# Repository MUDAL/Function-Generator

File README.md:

# Function-Generator

## Description  

This custom function generator is capable of outputting sine, square, and triangle waves of variable amplitude and frequency. An extra requirement of this device is its ability to produce DC voltages of adjustable magnitude and polarity.  

## Repository Layout
```
.
├── 3D_Models
├── Diagrams
├── Firmware
├── Images
├── LICENSE
├── PCB
├── README.md
└── Simulation
```

## Video Demos  
1. [Introduction and setup](https://drive.google.com/file/d/1G1p_1wfvQfPOZcchX9nzK7hOxaMMsMGi/view?usp=sharing)  
2. [System components](https://drive.google.com/file/d/1G7yjkzn5fIc1sIlq5uEcu3o-C55AYfCc/view?usp=sharing)   
3. [Amplitude control](https://drive.google.com/file/d/1G8uY1fm0E4KQyqx2Z7YYd4BkqQ50rcqq/view?usp=drive_link)    
4. [Waveform selection](https://drive.google.com/file/d/1GDZh32V0VEGifeL3dQ4JVQDjZ7OjrVeD/view?usp=sharing)   
5. [Frequency adjustment](https://drive.google.com/file/d/1HKlgbLmxHBRYYwaI7JoV4cJPAN9Vxr-B/view?usp=sharing)   
6. [DC magnitude and polarity control](https://drive.google.com/file/d/1HQdHPNzv4oxDs-NsEo27Fcs3HjVcjQDH/view?usp=sharing)    

## Images

## Helpful resources  
- [Rail splitter circuit with virtual push-pull topology: Discussion on EEVBlog](https://www.eevblog.com/forum/beginners/virtual-ground-push-pull/)
- [How the power supply rail splitter circuit works: An article written by Apichet Garaipoom](https://www.eleccircuit.com/power-supply-splitter-circuit-using-op-amp/)
- [EEVBlog discussion on high speed operational amplifiers](https://www.eevblog.com/forum/beginners/op-amp-bandwidth-and-is-there-an-affordable-fast-op-amp/)    
- [What is Slew Rate all about?](https://www.sciencedirect.com/topics/engineering/slew-rate)
- [Reddit discussion on high speed operational amplifiers](https://www.reddit.com/r/AskElectronics/comments/186d19x/high_speed_high_power_opamps/?rdt=65066)
- [Ivanchenko59: AD9833-DDS-Generator STM32 library](https://github.com/Ivanchenko59/AD9833-DDS-Generator/tree/master)
- [Mahamudul Hasan: Interfacing STM32 with I2C LCD: HAL example code included](https://embeddedthere.com/interfacing-stm32-with-i2c-lcd-with-hal-code-example/)
- [AD9833 Programmable Waveform Generator: Datasheet](https://www.analog.com/media/en/technical-documentation/data-sheets/AD9833.pdf)
- [STM32 Blue Pill 3D model by Denshi Kousaku](https://grabcad.com/library/stm32f103c8t6-blue-pill-board-1)
- [BNC Connector 3D model by Daniel Forero Morales](https://grabcad.com/library/bnc-connector--2)

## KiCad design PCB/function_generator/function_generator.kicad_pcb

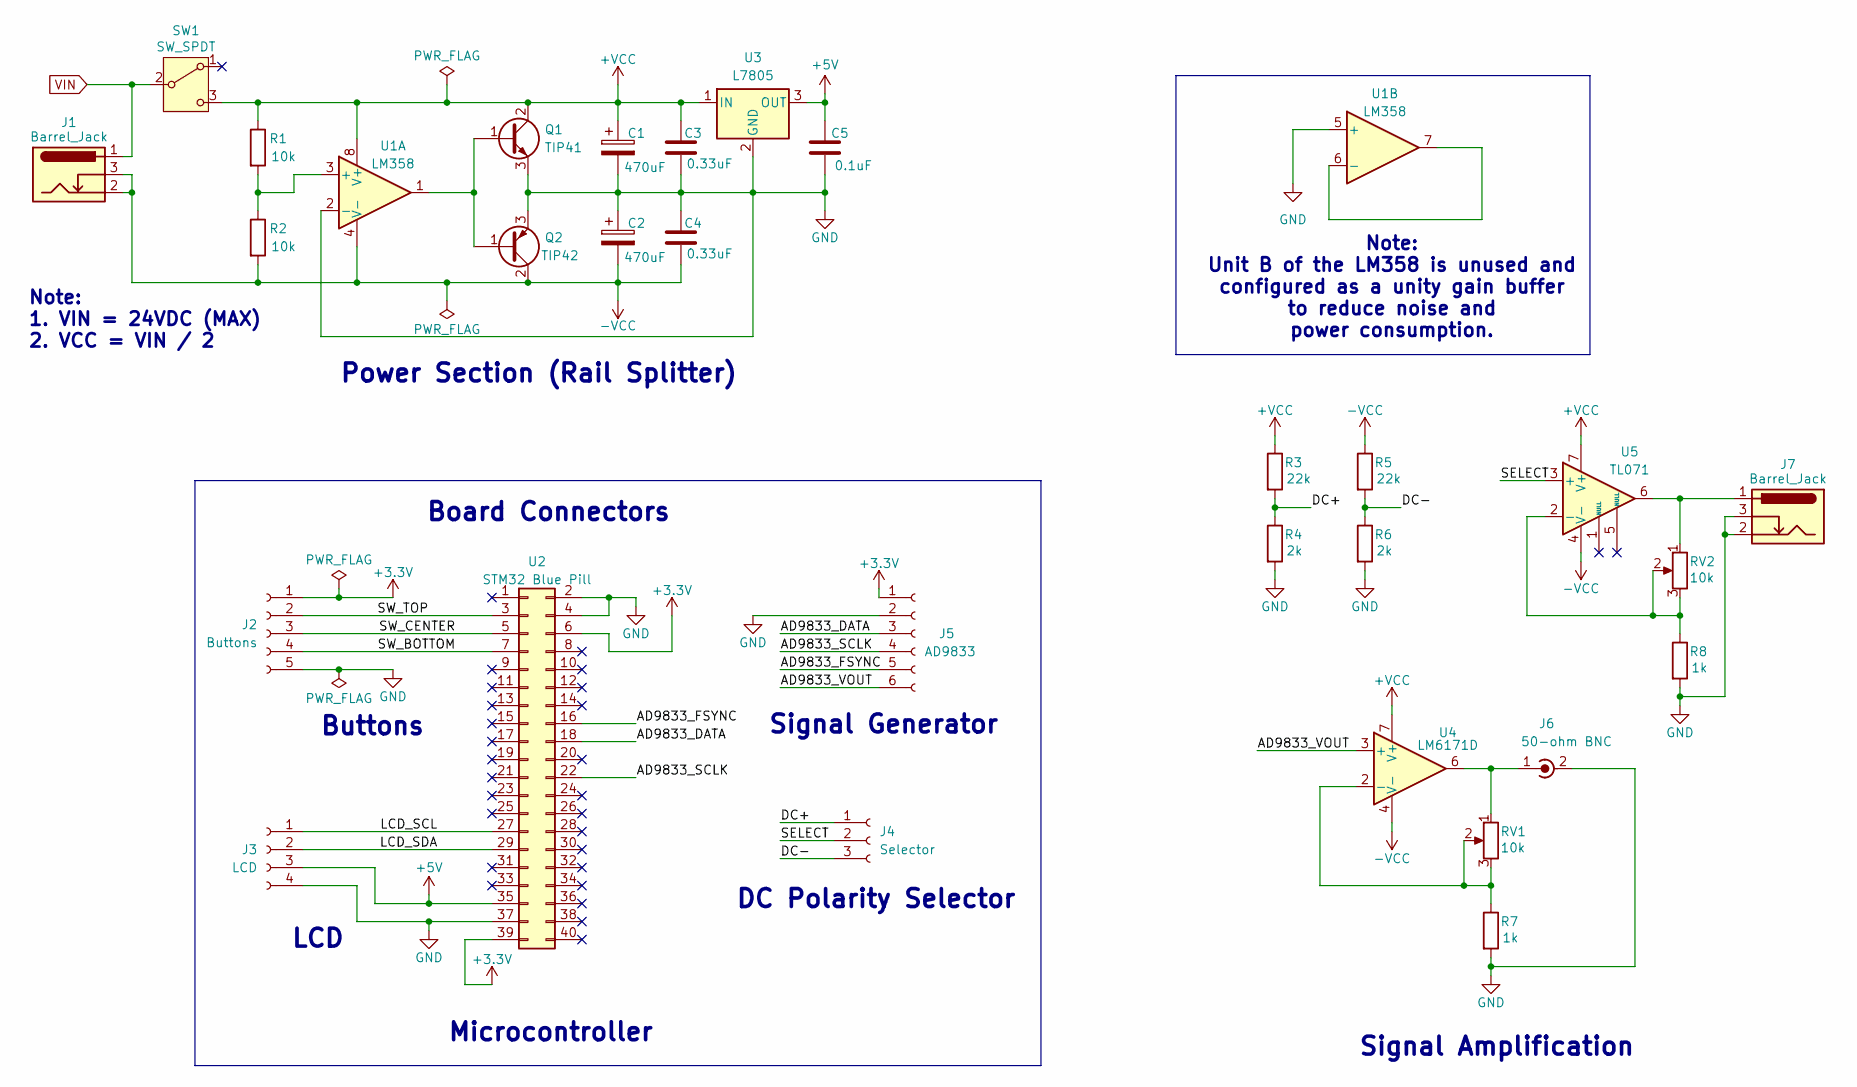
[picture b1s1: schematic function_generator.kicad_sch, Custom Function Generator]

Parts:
C1, C2: 470uF; CP_Radial_D10.0mm_P5.00mm
C3, C4: 0.33uF; C_Disc_D4.3mm_W1.9mm_P5.00mm
C5: 0.1uF; C_Disc_D4.3mm_W1.9mm_P5.00mm
J1, J7: Barrel_Jack; PinHeader_1x03_P2.54mm_Vertical
J2: Buttons; PinHeader_1x05_P2.54mm_Vertical
J3: LCD; PinHeader_1x04_P2.54mm_Vertical
J4: Selector; PinHeader_1x03_P2.54mm_Vertical
J5: AD9833; PinSocket_1x06_P2.54mm_Vertical
J6: 50-ohm BNC; BNC_Amphenol_B6252HB-NPP3G-50_Horizontal
Q1: TIP41; TO-220-3_Vertical
Q2: TIP42; TO-220-3_Vertical
R1, R2: 10k; R_Axial_DIN0207_L6.3mm_D2.5mm_P7.62mm_Horizontal
R3, R5: 22k; R_Axial_DIN0207_L6.3mm_D2.5mm_P7.62mm_Horizontal
R4, R6: 2k; R_Axial_DIN0207_L6.3mm_D2.5mm_P7.62mm_Horizontal
R7, R8: 1k; R_Axial_DIN0207_L6.3mm_D2.5mm_P7.62mm_Horizontal
RV1, RV2: 10k; PinHeader_1x03_P2.54mm_Vertical
SW1: SW_SPDT; PinHeader_1x03_P2.54mm_Vertical
U1: LM358; DIP-8_W7.62mm
U2: STM32 Blue Pill; Blue_Pill
U3: L7805; TO-220-3_Vertical
U4: LM6171D; SOIC-8_3.9x4.9mm_P1.27mm
U5: TL071; DIP-8_W7.62mm

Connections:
+3.3V: J2.1, J5.1, U2.6, U2.39
+5V: C5.1, J3.3, U2.35, U3.3 (OUT)
+VCC: C1.1, C3.1, Q1.2 (C), R1.1, R3.1, SW1.3 (C), U1.8 (V+), U3.1 (IN), U4.7 (V+), U5.7 (V+)
-VCC: C2.2, C4.2, J1.2, J1.3, Q2.2 (C), R2.2, R5.1, U1.4 (V-), U4.4 (V-), U5.4 (V-)
/AD9833_DATA: J5.3, U2.18
/AD9833_FSYNC: J5.5, U2.16
/AD9833_SCLK: J5.4, U2.22
/AD9833_VOUT: J5.6, U4.3 (+)
/DC+: J4.1, R3.2, R4.1
/DC-: J4.3, R5.2, R6.1
/LCD_SCL: J3.1, U2.27
/LCD_SDA: J3.2, U2.29
/SELECT: J4.2, U5.3 (+)
/SW_BOTTOM: J2.4, U2.7
/SW_CENTER: J2.3, U2.5
/SW_TOP: J2.2, U2.3
GND: C1.2, C2.1, C3.2, C4.1, C5.2, J2.5, J3.4, J5.2, J6.2 (Ext), J7.2, J7.3, Q1.3 (E), Q2.3 (E), R4.2, R6.2, R7.2, R8.2, U1.2 (-), U1.5 (+), U2.2, U2.4, U2.37, U3.2 (GND)
unnamed: J6.1 (In), RV1.1, U4.6
unnamed: J7.1, RV2.1, U5.6
unnamed: Q1.1 (B), Q2.1 (B), U1.1
unnamed: R1.2, R2.1, U1.3 (+)
unnamed: U1.6 (-), U1.7
unnamed: R7.1, RV1.2, RV1.3, U4.2 (-)
unnamed: R8.1, RV2.2, RV2.3, U5.2 (-)
VIN: J1.1, SW1.2 (B)

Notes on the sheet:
Board Connectors
LCD
Signal Amplification
Microcontroller
Note: 1. VIN = 24VDC (MAX) 2. VCC = VIN / 2
Signal Generator
DC Polarity Selector
Power Section (Rail Splitter)
Note: Unit B of the LM358 is unused and configured as a unity gain buffer to reduce noise and power consumption.
Buttons

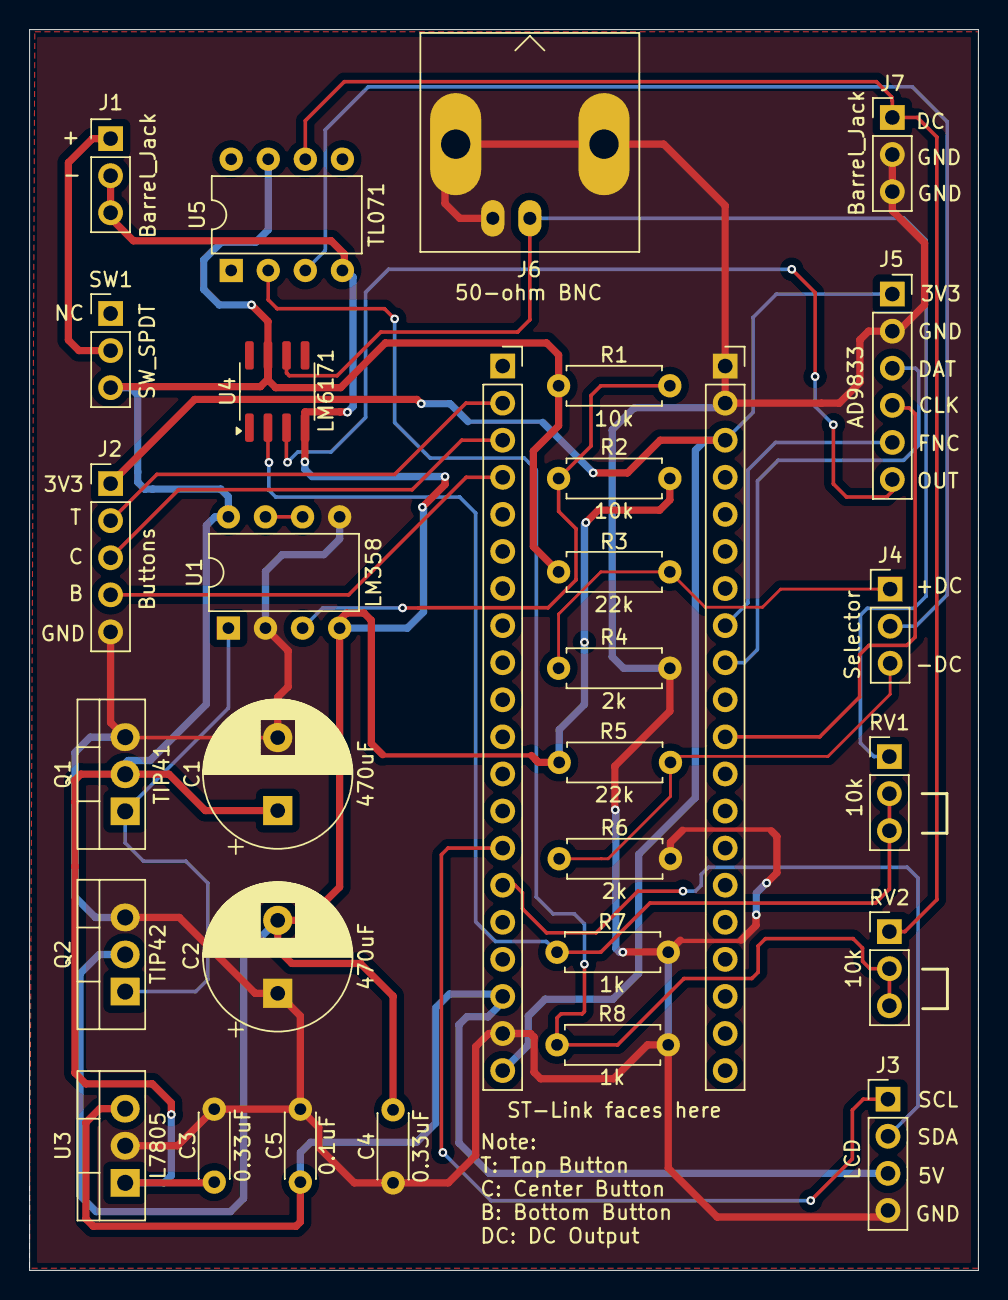
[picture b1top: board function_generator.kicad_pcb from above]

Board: 2 copper layers, 65.0 x 85.0 mm, 30 parts (0 on the bottom side), 25 nets.

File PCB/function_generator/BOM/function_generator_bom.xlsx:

Reference | Qty | Description | Manufacturer | Value | Footprint | DNP | Notes
U5 | 1 | Single Low-Noise JFET-Input Operational Amplifiers, DIP-8/SOIC-8 |  | TL071 | Package_DIP:DIP-8_W7.62mm | DNP
Q2 | 1 | -6A Ic, -40V Vce, Power PNP Transistor, TO-220 |  | TIP42 | Package_TO_SOT_THT:TO-220-3_Vertical | DNP
Q1 | 1 | 6A Ic, 40V Vce, Power NPN Transistor, TO-220 |  | TIP41 | Package_TO_SOT_THT:TO-220-3_Vertical | DNP
SW1 | 1 | Switch, single pole double throw |  | SW_SPDT | Connector_PinHeader_2.54mm:PinHeader_1x03_P2.54mm_Vertical | DNP
U2 | 1 | STM32 Blue Pill board |  | STM32 Blue Pill | Blue_Pill:Blue_Pill | DNP
J4 | 1 | Generic connector, single row, 01x03, script generated |  | Selector | Connector_PinHeader_2.54mm:PinHeader_1x03_P2.54mm_Vertical | DNP
U4 | 1 | High Speed Low Power Low Distortion Voltage Feedback Amplifier, SOIC-8 | Texas Instruments | LM6171 | Package_SO:SOIC-8_3.9x4.9mm_P1.27mm |  | SMD component. Assemble only this
U1 | 1 | Low-Power, Dual Operational Amplifiers, DIP-8/SOIC-8/TO-99-8 |  | LM358 | Package_DIP:DIP-8_W7.62mm | DNP
J3 | 1 | Generic connector, single row, 01x04, script generated |  | LCD | Connector_PinHeader_2.54mm:PinHeader_1x04_P2.54mm_Vertical | DNP
U3 | 1 | Positive 1.5A 35V Linear Regulator, Fixed Output 5V, TO-220/TO-263/TO-252 |  | L7805 | Package_TO_SOT_THT:TO-220-3_Vertical | DNP
J2 | 1 | Generic connector, single row, 01x05, script generated |  | Buttons | Connector_PinHeader_2.54mm:PinHeader_1x05_P2.54mm_Vertical | DNP
J7 | 1 | DC Barrel Jack with an internal switch |  | Barrel_Jack | Connector_PinHeader_2.54mm:PinHeader_1x03_P2.54mm_Vertical | DNP
J1 | 1 | DC Barrel Jack with an internal switch |  | Barrel_Jack | Connector_PinHeader_2.54mm:PinHeader_1x03_P2.54mm_Vertical | DNP
J5 | 1 | Generic connector, single row, 01x06, script generated |  | AD9833 | Connector_PinSocket_2.54mm:PinSocket_1x06_P2.54mm_Vertical | DNP
R5 | 1 | Resistor |  | 22k | Resistor_THT:R_Axial_DIN0207_L6.3mm_D2.5mm_P7.62mm_Horizontal | DNP
R3 | 1 | Resistor |  | 22k | Resistor_THT:R_Axial_DIN0207_L6.3mm_D2.5mm_P7.62mm_Horizontal | DNP
RV2 | 1 | Potentiometer |  | 10k | Connector_PinHeader_2.54mm:PinHeader_1x03_P2.54mm_Vertical | DNP
RV1 | 1 | Potentiometer |  | 10k | Connector_PinHeader_2.54mm:PinHeader_1x03_P2.54mm_Vertical | DNP
R2 | 1 | Resistor |  | 10k | Resistor_THT:R_Axial_DIN0207_L6.3mm_D2.5mm_P7.62mm_Horizontal | DNP
R1 | 1 | Resistor |  | 10k | Resistor_THT:R_Axial_DIN0207_L6.3mm_D2.5mm_P7.62mm_Horizontal | DNP
R6 | 1 | Resistor |  | 2k | Resistor_THT:R_Axial_DIN0207_L6.3mm_D2.5mm_P7.62mm_Horizontal | DNP
R4 | 1 | Resistor |  | 2k | Resistor_THT:R_Axial_DIN0207_L6.3mm_D2.5mm_P7.62mm_Horizontal | DNP
R8 | 1 | Resistor |  | 1k | Resistor_THT:R_Axial_DIN0207_L6.3mm_D2.5mm_P7.62mm_Horizontal | DNP
R7 | 1 | Resistor |  | 1k | Resistor_THT:R_Axial_DIN0207_L6.3mm_D2.5mm_P7.62mm_Horizontal | DNP
J6 | 1 | coaxial connector (BNC, SMA, SMB, SMC, Cinch/RCA, LEMO, ...) |  | 50-ohm BNC | Connector_Coaxial:BNC_Amphenol_B6252HB-NPP3G-50_Horizontal | DNP
C2 | 1 | Polarized capacitor |  | 470uF | Capacitor_THT:CP_Radial_D10.0mm_P5.00mm | DNP
C1 | 1 | Polarized capacitor |  | 470uF | Capacitor_THT:CP_Radial_D10.0mm_P5.00mm | DNP
C4 | 1 | Unpolarized capacitor |  | 0.33uF | Capacitor_THT:C_Disc_D4.3mm_W1.9mm_P5.00mm | DNP
C3 | 1 | Unpolarized capacitor |  | 0.33uF | Capacitor_THT:C_Disc_D4.3mm_W1.9mm_P5.00mm | DNP
C5 | 1 | Unpolarized capacitor |  | 0.1uF | Capacitor_THT:C_Disc_D4.3mm_W1.9mm_P5.00mm | DNP

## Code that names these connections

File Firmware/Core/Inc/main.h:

/* USER CODE BEGIN Header */
/**
  ******************************************************************************
  * @file           : main.h
  * @brief          : Header for main.c file.
  *                   This file contains the common defines of the application.
  ******************************************************************************
  * @attention
  *
  * <h2><center>&copy; Copyright (c) 2024 STMicroelectronics.
  * All rights reserved.</center></h2>
  *
  * This software component is licensed by ST under BSD 3-Clause license,
  * the "License"; You may not use this file except in compliance with the
  * License. You may obtain a copy of the License at:
  *                        opensource.org/licenses/BSD-3-Clause
  *
  ******************************************************************************
  */
/* USER CODE END Header */

/* Define to prevent recursive inclusion -------------------------------------*/
#ifndef __MAIN_H
#define __MAIN_H

#ifdef __cplusplus
extern "C" {
#endif

/* Includes ------------------------------------------------------------------*/
#include "stm32f1xx_hal.h"

/* Private includes ----------------------------------------------------------*/
/* USER CODE BEGIN Includes */

/* USER CODE END Includes */

/* Exported types ------------------------------------------------------------*/
/* USER CODE BEGIN ET */

/* USER CODE END ET */

/* Exported constants --------------------------------------------------------*/
/* USER CODE BEGIN EC */

/* USER CODE END EC */

/* Exported macro ------------------------------------------------------------*/
/* USER CODE BEGIN EM */

/* USER CODE END EM */

/* Exported functions prototypes ---------------------------------------------*/
void Error_Handler(void);

/* USER CODE BEGIN EFP */

/* USER CODE END EFP */

/* Private defines -----------------------------------------------------------*/
#define AD9833_SCK_Pin GPIO_PIN_5
#define AD9833_SCK_GPIO_Port GPIOA
#define AD9833_DATA_Pin GPIO_PIN_7
#define AD9833_DATA_GPIO_Port GPIOA
#define AD9833_FSYNC_Pin GPIO_PIN_0
#define AD9833_FSYNC_GPIO_Port GPIOB
#define SW_TOP_Pin GPIO_PIN_13
#define SW_TOP_GPIO_Port GPIOB
#define SW_CENTER_Pin GPIO_PIN_14
#define SW_CENTER_GPIO_Port GPIOB
#define SW_BOTTOM_Pin GPIO_PIN_15
#define SW_BOTTOM_GPIO_Port GPIOB
#define LCD_SCL_Pin GPIO_PIN_6
#define LCD_SCL_GPIO_Port GPIOB
#define LCD_SDA_Pin GPIO_PIN_7
#define LCD_SDA_GPIO_Port GPIOB

/* USER CODE BEGIN Private defines */

/* USER CODE END Private defines */

#ifdef __cplusplus
}
#endif

#endif /* __MAIN_H */

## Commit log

2024-11-23 Added: PCB
2024-12-13 Added 3D models
2024-12-13 Added images
2024-12-16 Added images of the final project
2024-12-30 Added detailed block diagram for the Function Generator
2024-12-30 Added diagram for the user interface's state transitions
2024-12-31 Minor update
2024-12-31 Flowchart for waveform selection logic
2024-12-31 Update: Lighter colours for diagrams
2024-12-31 Slight update
2024-12-31 Added final diagram: Flowchart for frequency selection logic
2025-01-12 Function generator CubeMX report
2026-03-11 Add images to README.md
2026-06-11 [RJX]: Revisiting the repository for updates.
2026-06-11 [RJX]: Improved repository's structure, removing unnecessary build outputs and artefacts.
2026-06-11 [RJX]: Removed additional unnecessary build artefacts
2026-06-11 [RJX]: Corrected .gitignore mistake
2026-06-11 [RJX]: Extra comments in the .gitignore
2026-06-11 [RJX]: Renamed the 3D model for the STM32 Blue Pill board.
2026-06-11 [RJX]: Updated PCB files to rely on the relative paths of the 3D models for better version control.
2026-06-11 [RJX]: Deleted unnecessary files in the 3D model folder
2026-06-12 [RJX]: Added little description, repository layout, and links to videos.
2026-06-12 [RJX]: Shortened link names
